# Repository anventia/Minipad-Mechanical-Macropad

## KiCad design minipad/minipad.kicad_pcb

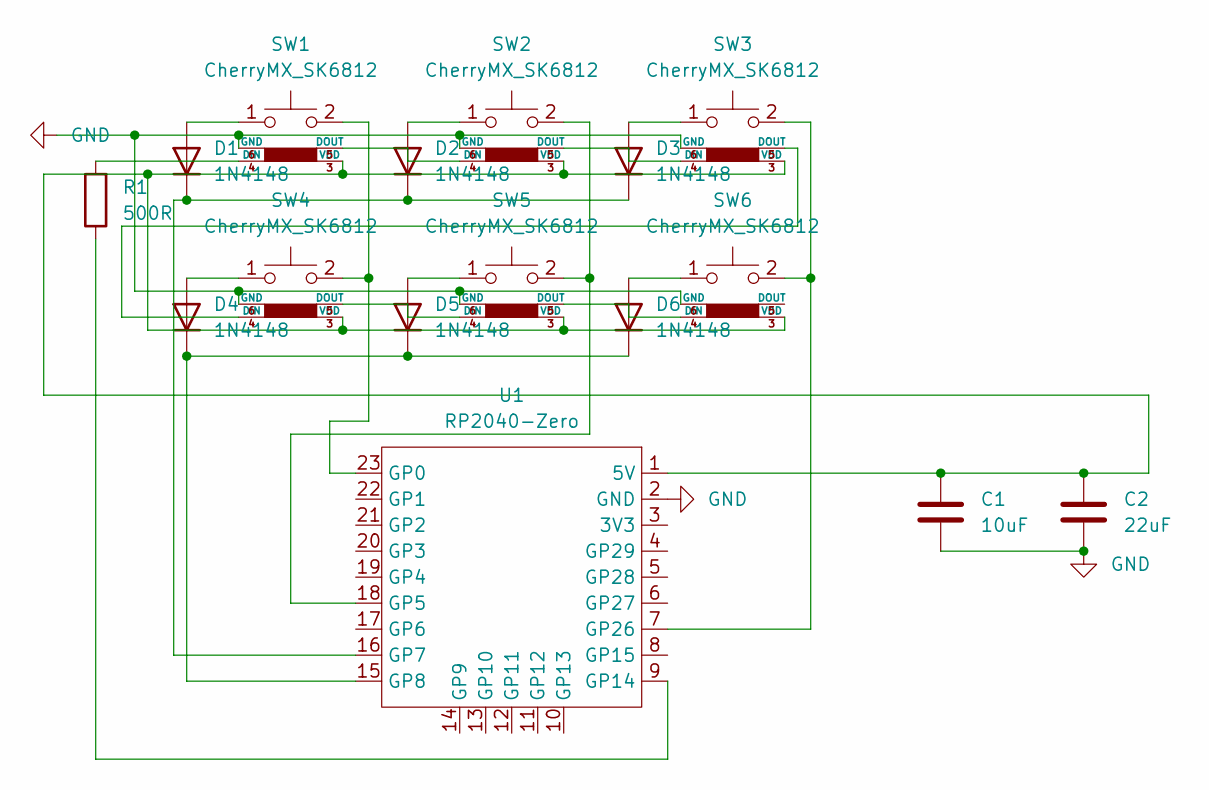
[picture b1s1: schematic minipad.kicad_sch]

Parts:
C1: 10uF; Cap_4mm_Horizontal
C2: 22uF; Cap_4mm_Horizontal
D1, D2, D3, D4, D5, D6: 1N4148; D_T-1_P5.08mm_Horizontal
R1: 500R; R_Axial_DIN0204_L3.6mm_D1.6mm_P7.62mm_Horizontal
SW1, SW2, SW3, SW4, SW5, SW6: CherryMX_SK6812; CMX-GLP_Hotswap_RGB_1.00u
U1: RP2040-Zero

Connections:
GND: C1.2, C2.2, SW1.6 (GND), SW2.6 (GND), SW3.6 (GND), SW4.6 (GND), SW5.6 (GND), SW6.6 (GND), U1.2 (GND)
unnamed: C1.1, C2.1, SW1.3 (VDD), SW2.3 (VDD), SW3.3 (VDD), SW4.3 (VDD), SW5.3 (VDD), SW6.3 (VDD), U1.1 (5V)
unnamed: D1.1 (K), D2.1 (K), D3.1 (K), U1.16 (GP7)
unnamed: D1.2 (A), SW1.1
unnamed: D2.2 (A), SW2.1
unnamed: D3.2 (A), SW3.1
unnamed: D4.1 (K), D5.1 (K), D6.1 (K), U1.15 (GP8)
unnamed: D4.2 (A), SW4.1
unnamed: D5.2 (A), SW5.1
unnamed: D6.2 (A), SW6.1
unnamed: R1.1, U1.9 (GP14)
unnamed: R1.2, SW1.4 (DIN)
unnamed: SW1.2, SW4.2, U1.23 (GP0)
unnamed: SW1.5 (DOUT), SW2.4 (DIN)
unnamed: SW2.2, SW5.2, U1.18 (GP5)
unnamed: SW2.5 (DOUT), SW3.4 (DIN)
unnamed: SW3.2, SW6.2, U1.7 (GP26)
unnamed: SW3.5 (DOUT), SW4.4 (DIN)
unnamed: SW4.5 (DOUT), SW5.4 (DIN)
unnamed: SW5.5 (DOUT), SW6.4 (DIN)

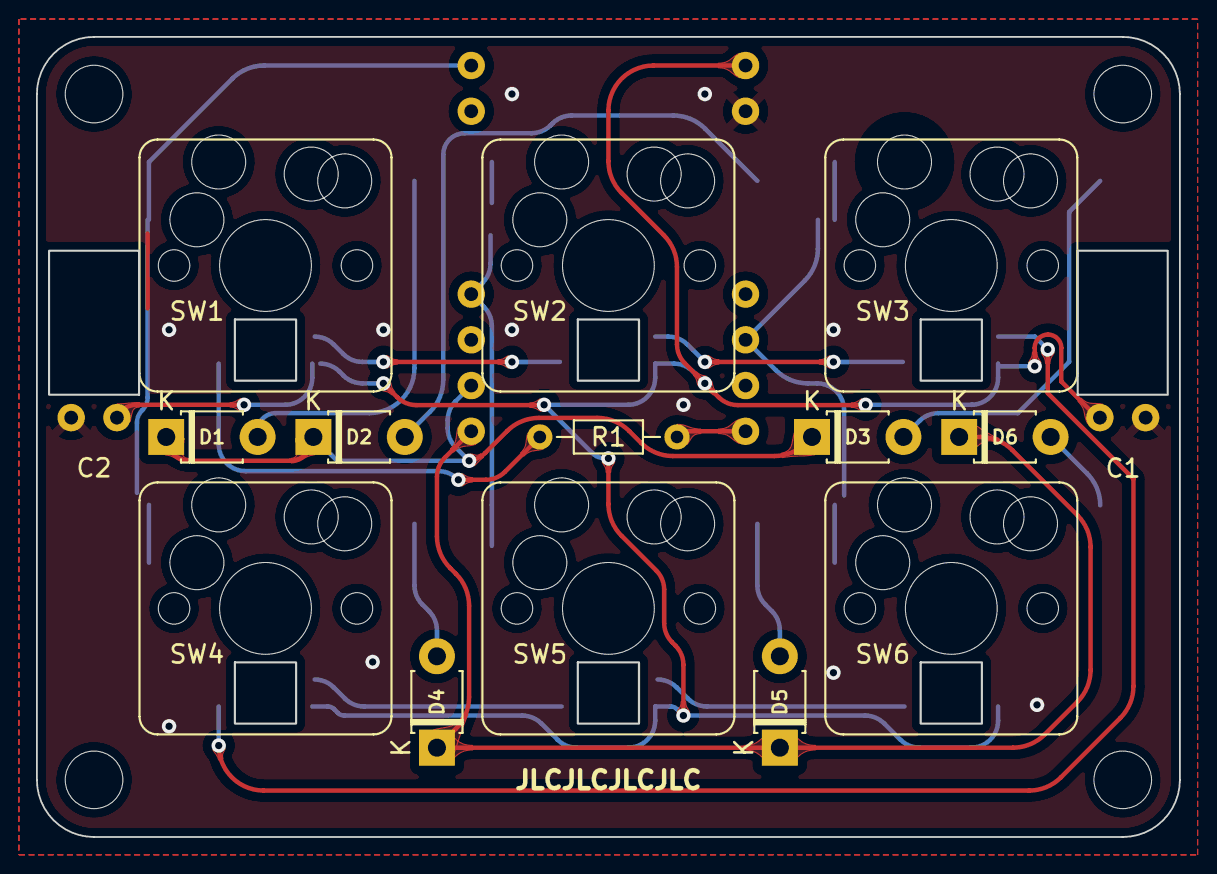
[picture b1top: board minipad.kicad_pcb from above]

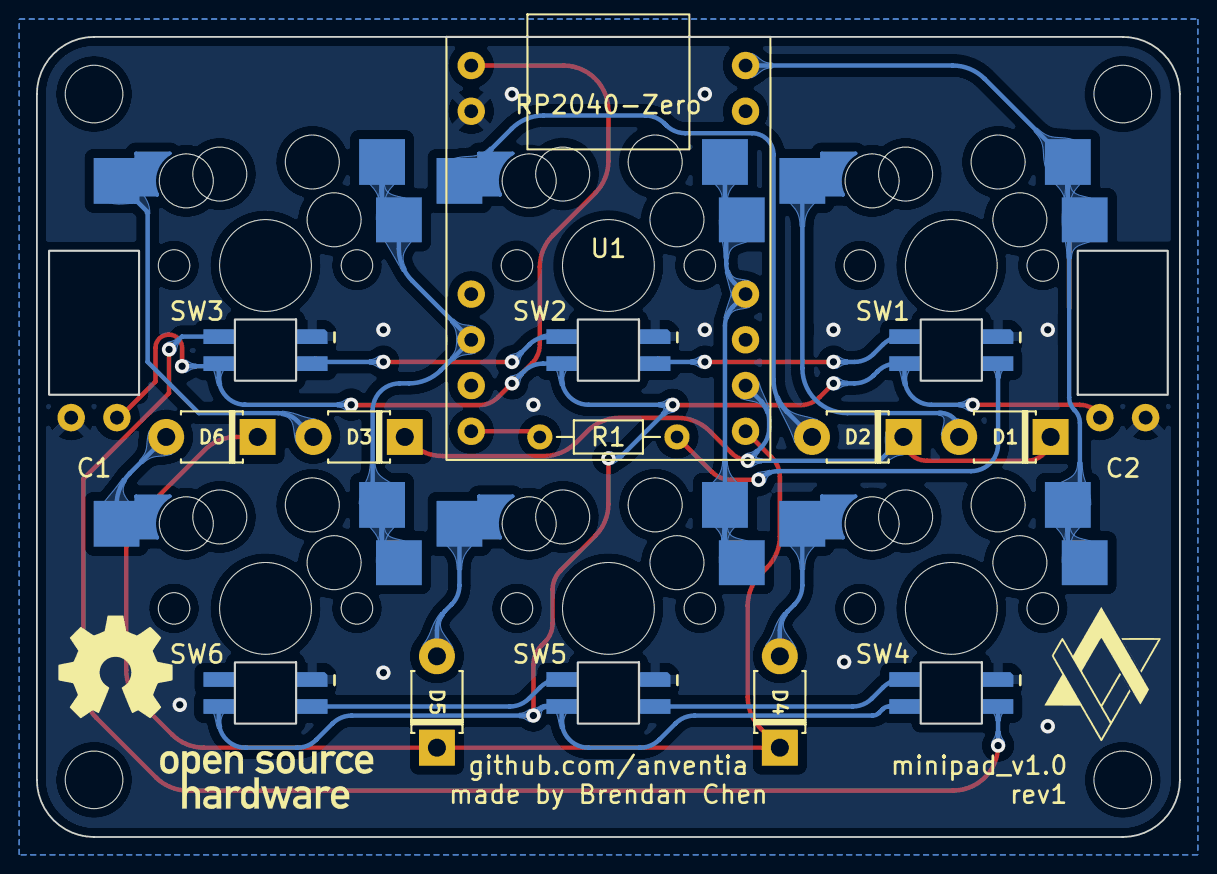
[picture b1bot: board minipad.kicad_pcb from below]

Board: 2 copper layers, 63.5 x 44.4 mm, 16 parts (2 on the bottom side), 20 nets.

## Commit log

2022-08-28 Generated Gerber files and ordered PCBs
2022-09-15 Removed extra circle
